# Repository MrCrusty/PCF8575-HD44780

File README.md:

# PCF8575-HD44780

# The Kicad 10.x 3D rendered image above shows a PCB designed to use a PCF8575 I2C two port 8bit custom interface for HD44780 LCD's

# A C99 Software driver is provided for STM32 "BlackPill" development board, which should be easily modifed for other MCU's
 
### Hitachi brought the HD44780 to market 40 years ago, at that time I was just turning 40 and in that year my employer complained at the exhorbitant cost of using this display in a digital multimeter that could have quite have easily been an off the peg analogue AVO.

### Today these LCd's are sub £5.00 for a 4 line by 20 character display. However interfacing this LCD in it's native 8bit data bus mode uses to many I/O pins on an embeded MCU design. The solution has been to use I2C interface modules notably the PCF8574 which has become popular as they only require the MCU to use 2 I/O pins (SDA and SCK) to effect communication between the LCD and the MCU. 

image curtosy of "Cricklewood Electronics"

There is to my knowledge only one 8 Bit I2C interface specifically sold to interface directly with the pins of an HD44780LCD display

#### There is a lot of excelent code that suports these I2C port extender modules. There is a trade off with using only an 8 bit extender port which is that the display has to be operated in 4 bit bus mode so that the other 4 bits can be used for the displays control lines. Whilst there is a lot of code for writing to a display in 4 bit mode, there is a very limited amount of code to be found for reading the display memory in 4 bit mode. 

## So is it possible to write to the Hd44780 with I2C in 8 bit mode yes it is not very difficult and a commercial module for doing this is as shown below

image curtosy of "diymore Alice1101983 Store"
  
It uses the MCP23017 chip to provide all the control bits and data bits required to run an hd44780 LCD in 8 bit mode. I have written code for it to run on a STM32 "BlackPill" development board. It works, its fast, and it easily reads the memory from the HD44780 bus. 

## So why design and build my own I2C dual 8 bit port device using the PCF8575 the answer is that the MCP23017 chip needs at least one more I/O pin to be supplied by the MCU in the guise of a reset line, this is essential in my view as the adressing mode of the device can be two diferent options. The other problem for me is that it has far more registers than I need to run the LCD.

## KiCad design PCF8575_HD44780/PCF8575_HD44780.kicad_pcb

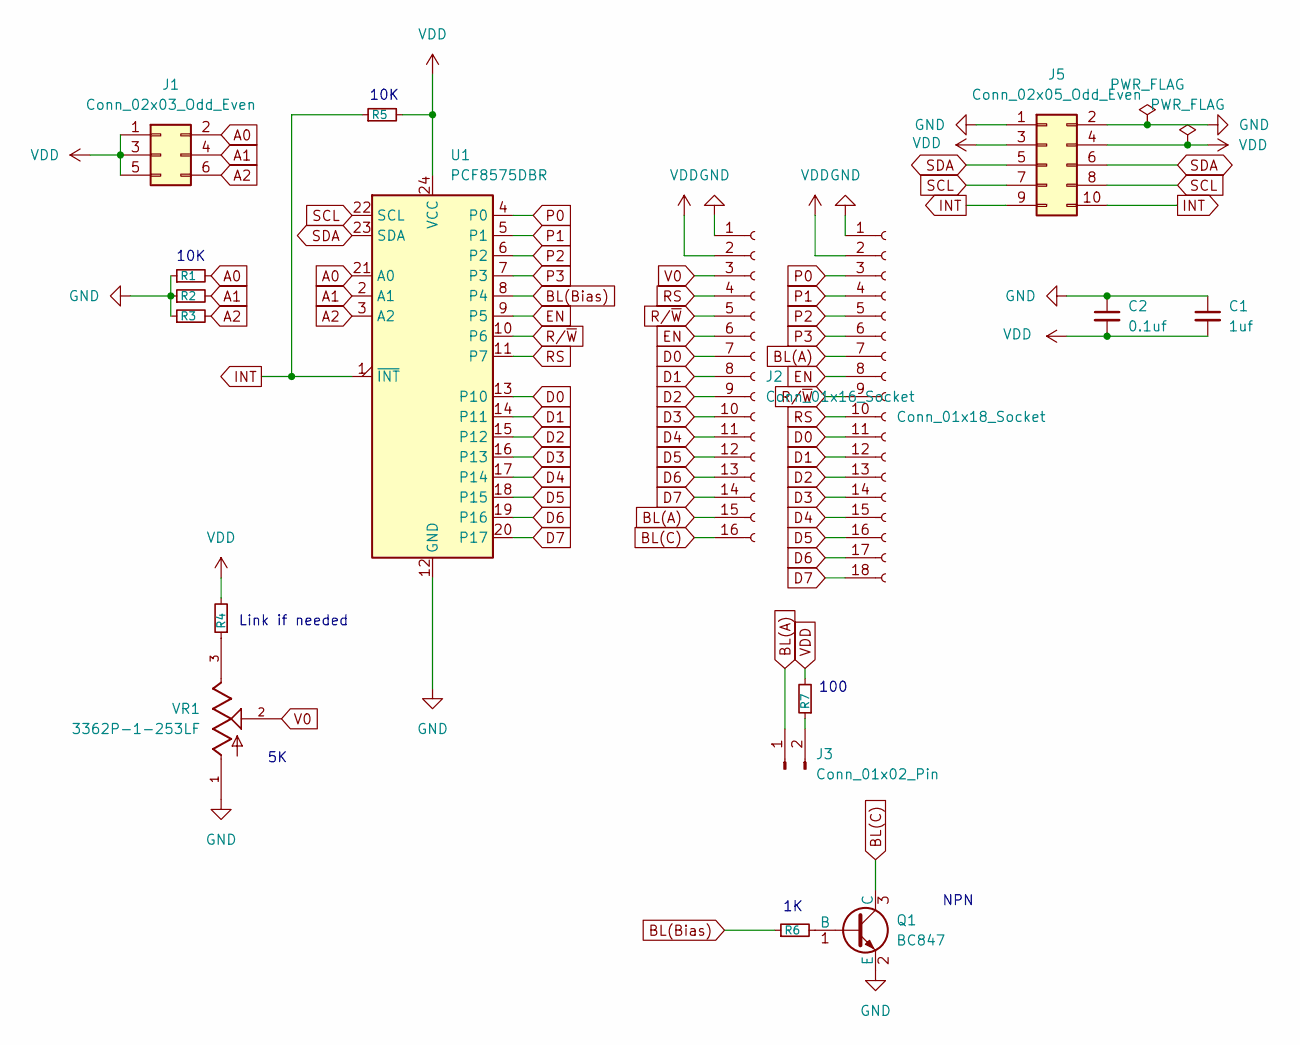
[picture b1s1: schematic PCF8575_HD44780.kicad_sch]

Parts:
C1: 1uf; C_0805_2012Metric_Pad1.18x1.45mm_HandSolder
C2: 0.1uf; C_0805_2012Metric
J1: Conn_02x03_Odd_Even; PinHeader_2x03_P2.54mm_Vertical
J2: Conn_01x16_Socket; PinHeader_1x16_P2.54mm_Vertical
J3: Conn_01x02_Pin; PinHeader_1x02_P2.54mm_Vertical
J4: Conn_01x18_Socket; PinHeader_1x18_P2.54mm_Vertical
J5: Conn_02x05_Odd_Even; PinSocket_2x05_P2.54mm_Vertical
Q1: BC847; SOT-23
R1, R2, R3, R4, R5, R6, R7: R_Small; R_0805_2012Metric
U1: PCF8575DBR; SSOP-24_5.3x8.2mm_P0.65mm
VR1: 3362P-1-253LF; TRIM_3362P-1-253LF; PARTREV 08/26/10

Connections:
A0: J1.2, R1.2, U1.21 (A0)
A1: J1.4, R2.2, U1.2 (A1)
A2: J1.6, R3.2, U1.3 (A2)
BL(A): J2.15, J3.1, J4.7
BL(Bias): R6.1, U1.8 (P4)
BL(C): J2.16, Q1.3 (C)
D0: J2.7, J4.11, U1.13 (P10)
D1: J2.8, J4.12, U1.14 (P11)
D2: J2.9, J4.13, U1.15 (P12)
D3: J2.10, J4.14, U1.16 (P13)
D4: J2.11, J4.15, U1.17 (P14)
D5: J2.12, J4.16, U1.18 (P15)
D6: J2.13, J4.17, U1.19 (P16)
D7: J2.14, J4.18, U1.20 (P17)
EN: J2.6, J4.8, U1.9 (P5)
GND: C1.1, C2.1, J2.1, J4.1, J5.1, J5.2, Q1.2 (E), R1.1, R2.1, R3.1, U1.12 (GND), VR1.1
INT: J5.9, J5.10, R5.1, U1.1 (~INT)
unnamed: J3.2, R7.1
unnamed: Q1.1 (B), R6.2
unnamed: R4.1, VR1.3
P0: J4.3, U1.4 (P0)
P1: J4.4, U1.5 (P1)
P2: J4.5, U1.6 (P2)
P3: J4.6, U1.7 (P3)
RS: J2.4, J4.10, U1.11 (P7)
R/~W: J2.5, J4.9, U1.10 (P6)
SCL: J5.7, J5.8, U1.22 (SCL)
SDA: J5.5, J5.6, U1.23 (SDA)
V0: J2.3, VR1.2
VDD: C1.2, C2.2, J1.1, J1.3, J1.5, J2.2, J4.2, J5.3, J5.4, R4.2, R5.2, R7.2, U1.24 (VCC)

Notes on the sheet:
100
10K
NPN
Link if needed

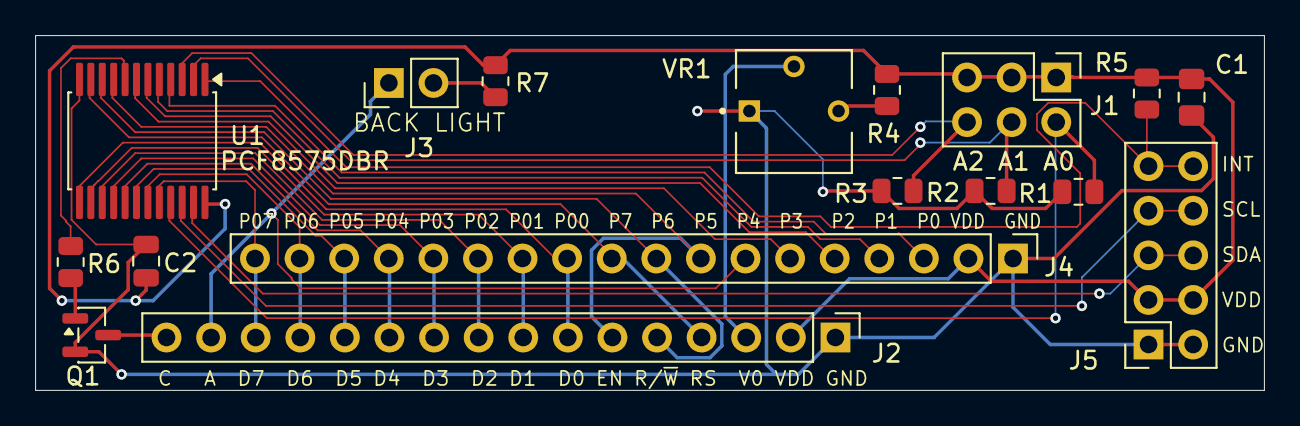
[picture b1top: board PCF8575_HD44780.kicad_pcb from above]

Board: 2 copper layers, 70.0 x 20.2 mm, 17 parts (0 on the bottom side), 30 nets.
